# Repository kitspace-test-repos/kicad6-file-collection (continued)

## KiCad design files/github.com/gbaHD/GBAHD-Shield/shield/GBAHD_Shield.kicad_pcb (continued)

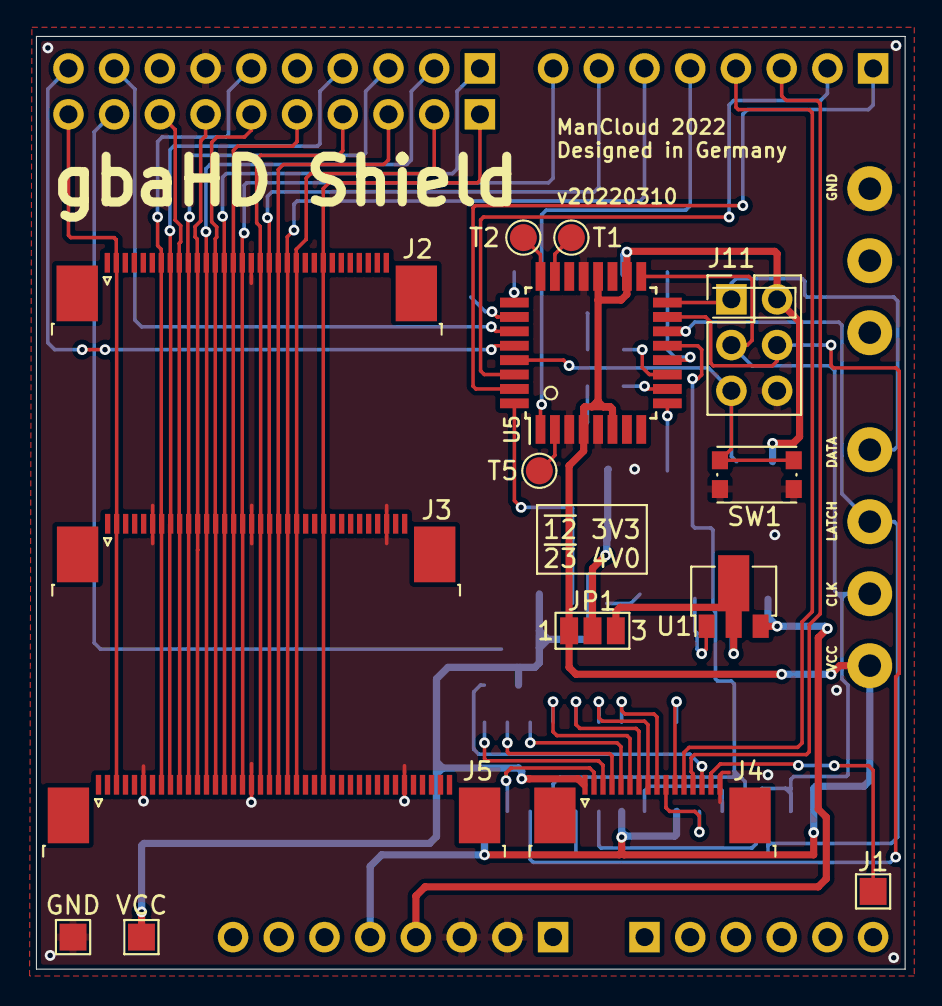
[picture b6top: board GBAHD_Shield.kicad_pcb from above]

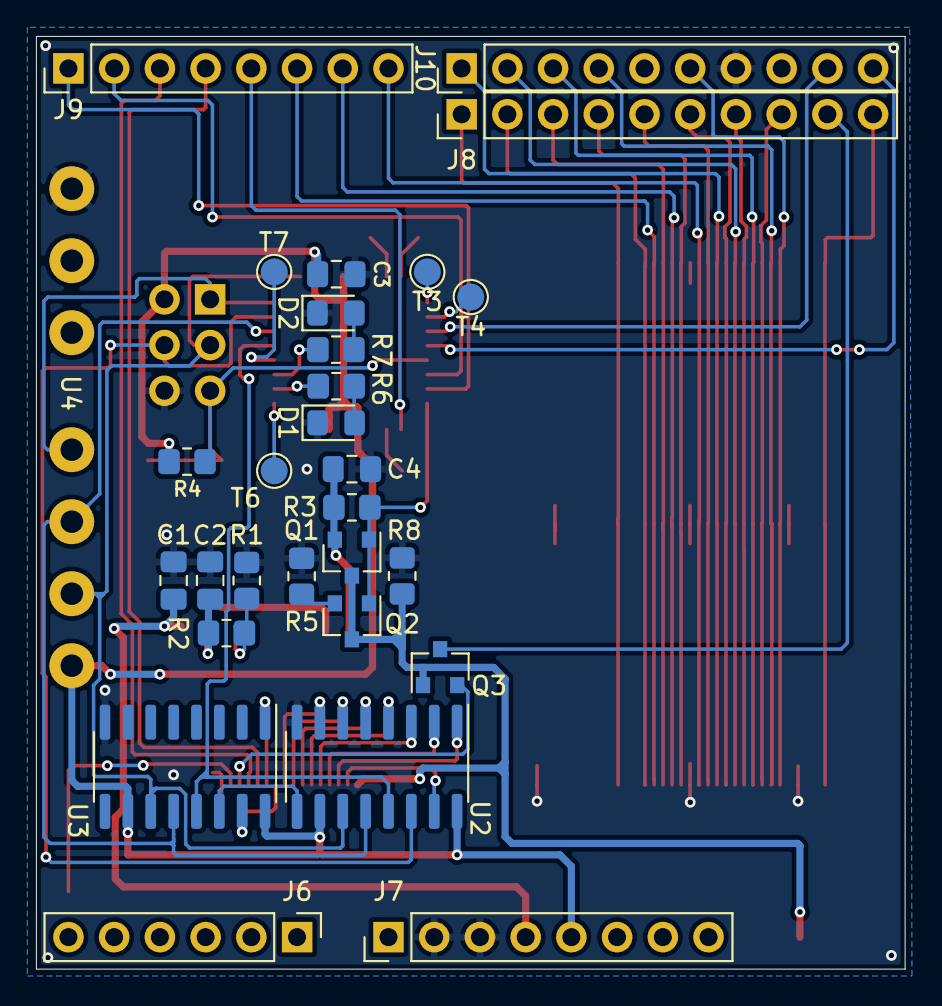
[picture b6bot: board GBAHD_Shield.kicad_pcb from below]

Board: 2 copper layers, 48.3 x 51.8 mm, 44 parts (29 on the bottom side), 64 nets.

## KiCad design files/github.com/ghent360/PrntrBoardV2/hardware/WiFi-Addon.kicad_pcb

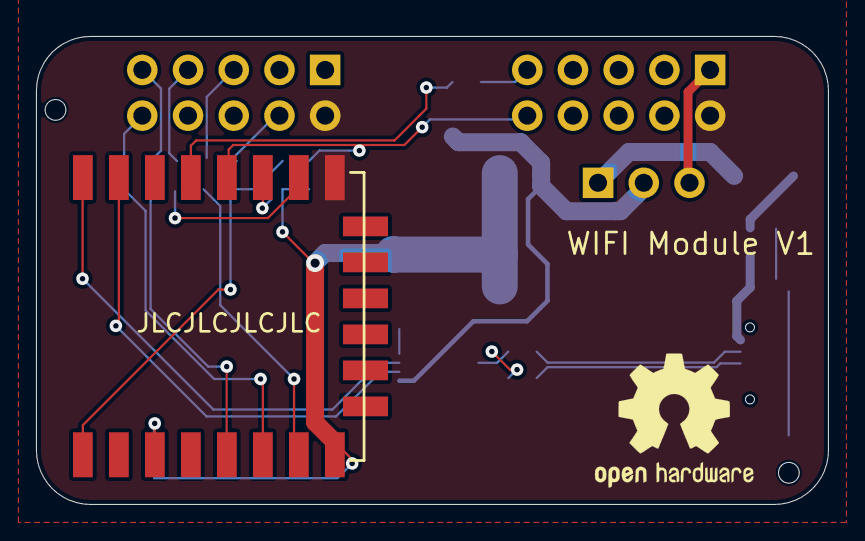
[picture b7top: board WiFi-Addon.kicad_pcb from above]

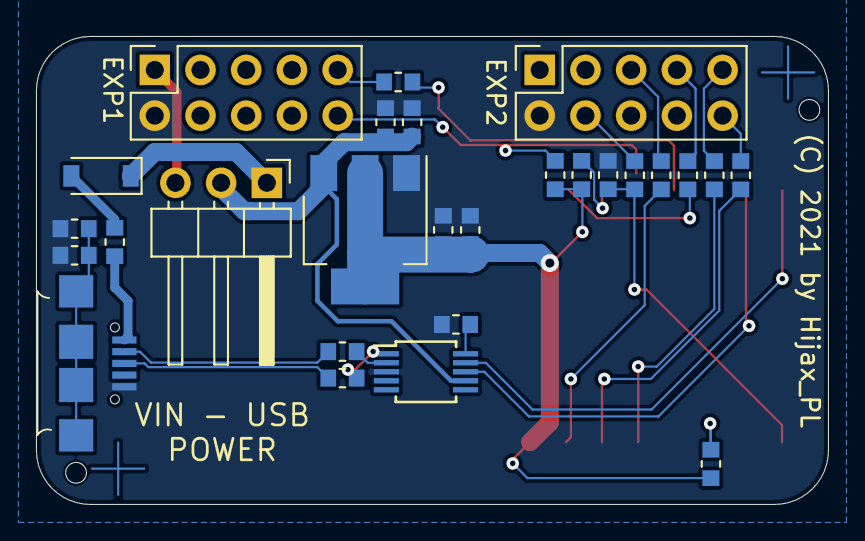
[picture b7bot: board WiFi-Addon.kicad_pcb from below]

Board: 2 copper layers, 44.0 x 26.0 mm, 33 parts (29 on the bottom side), 30 nets.

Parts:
C1, C4: 10uF; C_0603_1608Metric
C2, C3, C5, C19: 0.1uF; C_0603_1608Metric
C6: 10n; C_0603_1608Metric
D1: B5819W; D_SOD-123
EXP1, EXP2: IDC 2x5; PinSocket_2x05_P2.54mm_Vertical
F1: 500mA; R_0603_1608Metric
FID1, FID2: Fiducial; Fiducial_1mm_Dia_2.54mm_Outer_CopperTop
H1, H2: JLC Tooling Hole; JLC_Tool_hole
J1: PWR; PinHeader_1x03_P2.54mm_Horizontal
J3: USB_B_Micro; MC-101C
LOGO1: Logo_Open_Hardware_Small; OSHW-Logo2_9.8x8mm_SilkScreen
R1, R4, R6: 47R; R_0603_1608Metric
R2: 470R; R_0603_1608Metric
R3, R5: 2k2; R_0603_1608Metric
R7, R8, R13: 10k; R_0603_1608Metric
R10, R11: 22; R_0603_1608Metric
R12: 100k; R_0603_1608Metric
U1: AMS1117-3.3; SOT-223-3_TabPin2
U2: ESP-12F; ESP-12E_SMD
U3: CH340G; MSOP-10_3x3mm_P0.5mm

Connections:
3.3V: C3.1, C4.1, R7.2, R8.1, R13.1, U1.2 (VO), U2.8 (VCC)
5V: C1.1, C2.1, J1.2, U1.3 (VI), U3.7 (VCC)
/CSEL: EXP2.7, R5.1
/D+: J3.3 (D+), R11.1
/D-: J3.2 (D-), R10.1
/DATA_RDY: EXP1.10, R13.2, U2.12 (GPIO0)
/EN: R7.1, U2.3 (CH_PD)
/E_MISO: EXP2.10, R1.1
/E_MOSI: EXP2.5, R6.1
/E_RST: EXP2.4, R2.1
/E_SCK: EXP2.9, R4.1
/MISO: R1.2, U2.6 (GPIO12)
/MOSI: R6.2, U2.7 (GPIO13)
/RST: C5.2, R2.2, U2.1 (REST)
/SCK: R4.2, U2.5 (GPIO14)
/TRF_RDY: R3.2, U2.13 (GPIO4)
/VBUS: D1.1 (K), J1.1
/VIN: EXP1.1, J1.3
GND: C1.2, C2.2, C3.2, C4.2, C5.1, C6.1, C19.1, EXP1.2, EXP2.2, J3.5 (GND), R12.1, U1.1 (GND), U2.9 (GND), U3.3 (GND)
unnamed: C6.2, U3.10 (V3)
unnamed: C19.2, J3.6 (Shield), R12.2
unnamed: D1.2 (A), F1.2
unnamed: EXP1.9, R3.1
unnamed: F1.1, J3.1 (VBUS)
unnamed: R5.2, U2.10 (GPIO15)
unnamed: R8.2, U2.11 (GPIO2)
RX: U2.15 (RXD), U3.8 (TXD)
TX: U2.16 (TXD), U3.9 (RXD)
USB_D+: R11.2, U3.1 (UD+)
USB_D-: R10.2, U3.2 (UD-)

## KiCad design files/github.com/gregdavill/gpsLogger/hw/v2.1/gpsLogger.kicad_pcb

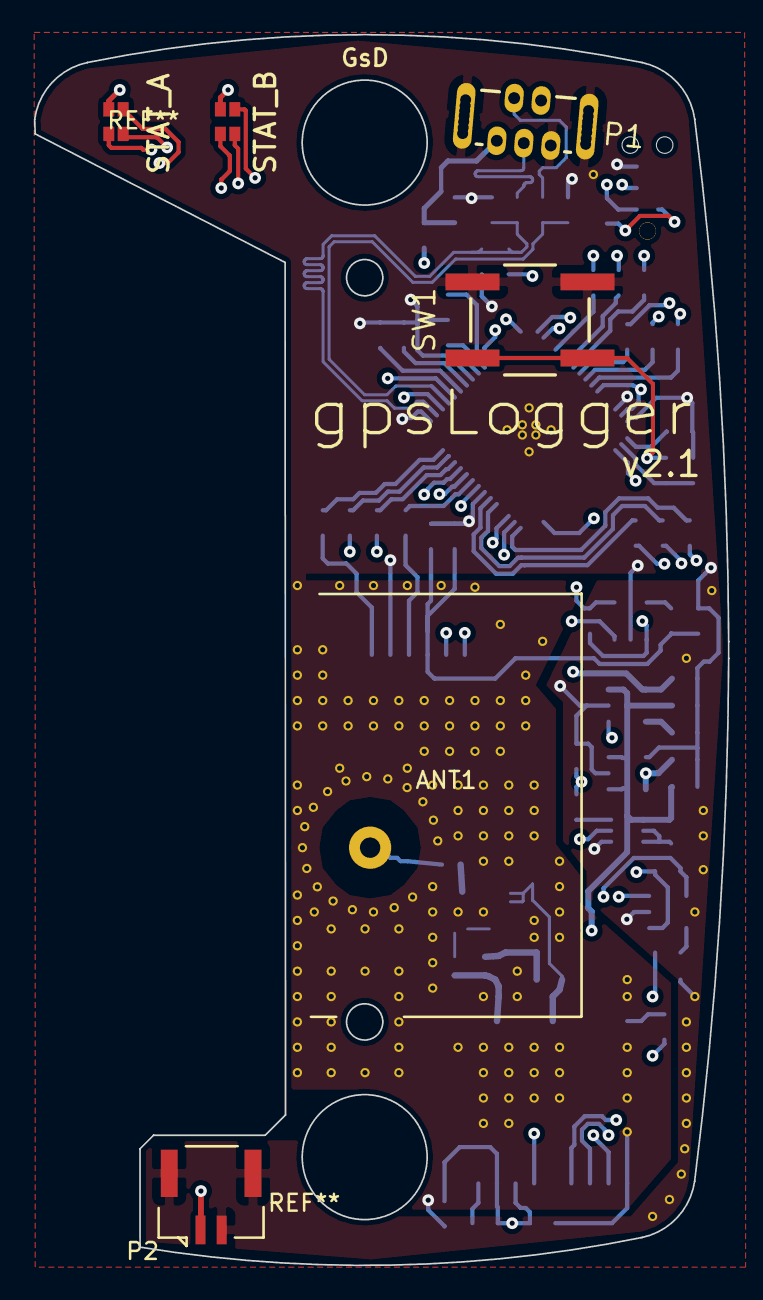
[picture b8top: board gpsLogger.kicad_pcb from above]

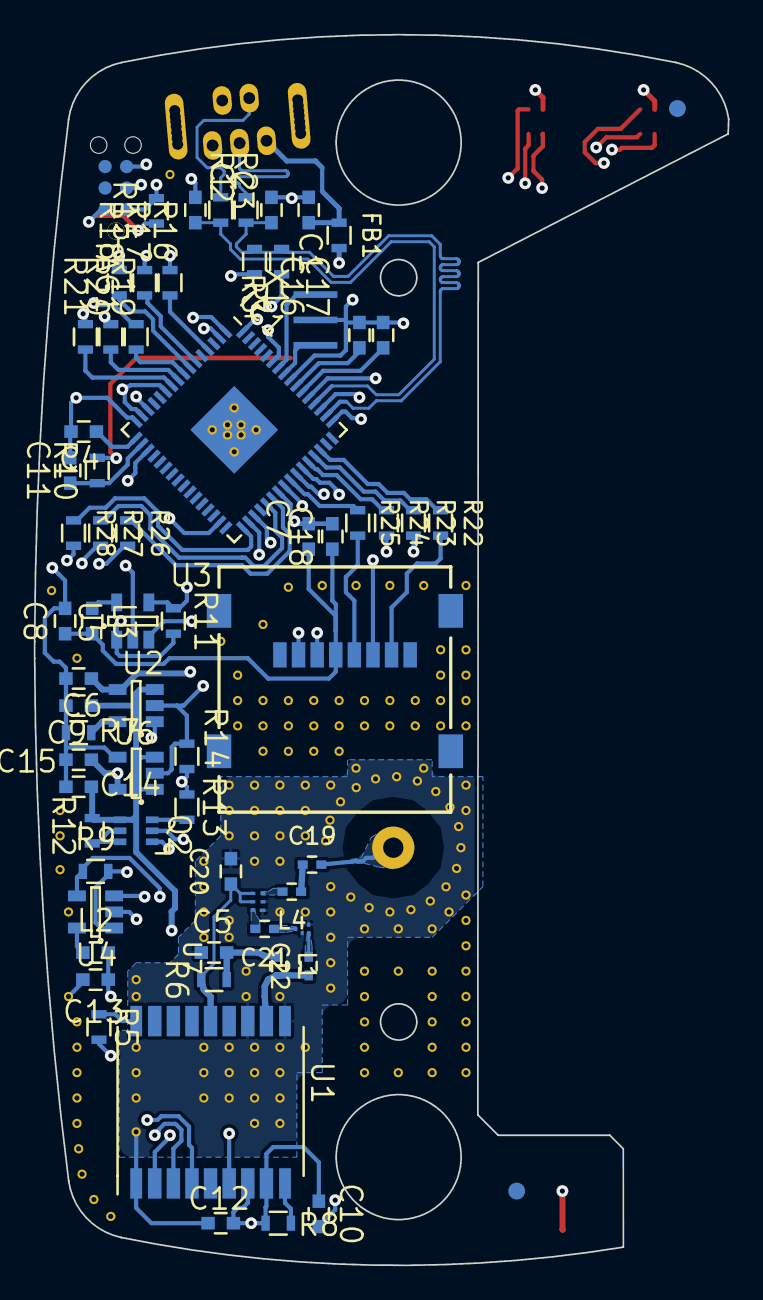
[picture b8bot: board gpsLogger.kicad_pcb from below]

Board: 4 copper layers, 41.0 x 72.8 mm, 73 parts (67 on the bottom side), 71 nets.

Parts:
ANT1: ANT; GPS_ANT
C1, C5, C7, C12: 10n; C_0603
C2, C3: 22p; C_0603
C4, C8, C13, C16, C17: 1uF; C_0603
C6, C9, C14, C15: C; C_0603
C10, C11, C18: 100n; C_0603
C19, C21, C22: 47pF; C_0402
C20: 1nF; C_0603
D1, D2: Led_RGB_CA; LITEON_RGB
FB1: 1k FB; R_0603
FLT1: B8813; SAW-5
IC1: MSP430F55xx; QFN-64-1EP_9x9mm_Pitch0.5mm
L1: 27nH; C_0402
L2, L3: 100nH; C_0603
L4: 5.6nH; C_0402
P1: USB_OTG; USB_VERT
P2: CONN_01X02; BM02B-GHS-TBT
Q2: FG6943010R; SC-70-6
R1, R2: 27R; R_0603
R3: 470k; R_0603
R4: 1k4; R_0603
R5, R8, R9, R11: 10k; R_0603
R6: 10R; R_0603
R7, R12, R13, R14, R15, R16, R17, R18, R19, R20, R21: R; R_0603
R10: 1k; R_0603
R22, R23, R24, R25, R26, R27, R28: 2k2; R_0603
SW1: SW_PUSH; EVQ_switch
TAG1: TAG_CONNECT; tag_connect
U1: MAX_M8Q; MAX_M8
U2: MCP73812; SOT-23-5
U3: uSD; SD_holder_472190001
U4, U5: MIC2091; SOT-23-5
U6: TPS78230; SOT-23-5
U7: BGU7007; XSON6
X1: CRYSTAL_SMD; CSTCR_G15C

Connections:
1v8: C16.1, IC1.55
+3V3: C15.1, D1.1, D2.1, IC1.11, IC1.15, IC1.40, R9.2, R11.2, R15.1, TAG1.2, U4.1, U5.1, U6.5
+BATT: C9.1, C14.1, P2.1, Q2.4, R12.1, U2.3, U6.1, U6.3
/ANT_RF: ANT1.1, C19.2
/LED_A_B: IC1.7, R18.2
/LED_A_G: IC1.6, R17.2
/LED_A_R: IC1.4, R16.2
/LED_B_B: IC1.10, R21.2
/LED_B_G: IC1.9, R20.2
/LED_B_R: IC1.8, R19.2
/OSC_IN: IC1.58, X1.1
/OSC_OUT: IC1.57, X1.2
/PUR: IC1.51, R4.1
/RST: IC1.64, R15.2, TAG1.1
/SENSE_EN: IC1.2, Q2.2
/TEST: IC1.59, TAG1.3
/USB_DATA_N: C2.1, IC1.52, R1.1
/USB_DATA_P: C3.1, IC1.50, R2.1, R3.2, R4.2
/USB_IN_N: P1.2, R1.2
/USB_IN_P: P1.3, R2.2
/V_SENSE: IC1.1, R13.2, R14.1
GND: C1.2, C2.2, C3.2, C4.2, C5.2, C6.2, C7.2, C8.2, C9.2, C10.2, C11.2, C12.2, C13.2, C14.2, C15.2, C16.2, C17.2, C18.2, C20.2, FLT1.2, FLT1.3, FLT1.5, IC1.14, IC1.16, IC1.39, IC1.49, IC1.56, IC1.65, P1.5, P1.6, P2.2, Q2.1, R3.1, R7.1, R14.2, SW1.2, TAG1.5, U1.1, U1.10, U1.12, U2.2, U3.6, U4.2, U5.2, U6.2, U6.4, U7.1, U7.2, X1.3
GPS_BACKUP: IC1.31, U1.6
GPS_MISO: R26.2, U1.2
GPS_MOSI: R27.2, U1.3
GPS_PPS: R28.2, U1.4
GPS_PWR: IC1.34, U4.3
GPS_PWR_FAULT: IC1.35, R9.1, U4.4
GPS_RF_IN: C22.1, L1.2, U1.11
GPS_VCC: C10.1, C12.1, C13.1, L2.2, R5.2, R8.1, U1.7, U1.8
GPS_VCC_RF: C20.1, R6.1, U1.14, U7.4, U7.5
MMC_CLK: R25.2, U3.5
MMC_CS: R24.2, U3.2
MMC_MISO: R22.2, U3.7
MMC_MOSI: R23.2, U3.3
MMC_PWR: IC1.42, U5.3
MMC_PWR_FAULT: IC1.43, R11.1, U5.4
MMC_VCC: C7.1, C8.1, C18.1, L3.2, U3.4
unnamed: C1.1, FB1.1, P1.1
unnamed: C4.1, IC1.17
unnamed: C5.1, L1.1, R6.2
unnamed: C19.1, L4.1
unnamed: C21.1, FLT1.1
unnamed: C21.2, U7.6
unnamed: C22.2, FLT1.4
unnamed: D1.2, R16.1
unnamed: D1.3, R17.1
unnamed: D1.4, R18.1
unnamed: D2.2, R19.1
unnamed: D2.3, R20.1
unnamed: D2.4, R21.1
unnamed: IC1.33, R28.1
unnamed: IC1.37, R27.1
unnamed: IC1.38, R26.1
unnamed: IC1.41, R25.1
unnamed: IC1.44, R24.1
unnamed: IC1.45, R23.1
unnamed: IC1.46, R22.1
unnamed: L2.1, U4.5
unnamed: L3.1, U5.5
unnamed: L4.2, U7.3
unnamed: Q2.3, R13.1
unnamed: Q2.5, Q2.6, R12.2
unnamed: R5.1, U1.18
unnamed: R7.2, U2.5
unnamed: R8.2, U1.9
unnamed: R10.2, SW1.1
PWR_BUT: C11.1, IC1.18, R10.1
VBUS: C6.1, FB1.2, IC1.53, U2.4
VUSB: C17.1, IC1.54
~CHG: IC1.19, U2.1
